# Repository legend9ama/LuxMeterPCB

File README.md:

# LuxMeter v1.0 - Hardware Datasheet

<div align="center">
  
</div>

**LuxMeter** started as a PCB design assignment for my *Fundamentals of Electronics* course.

The requirement was just to submit the layout files, but I decided to go all the way. I ordered the PCBAs and wrote the firmware.

This repository contains the hardware design files (KiCad), schematics, and manufacturing data.

---

## 📸 Gallery

| Top View | Bottom View |
| :---: | :---: |
|  | 

---

## 📐 Circuit Diagram (Schematic)

The full schematic design is available in the [`LuxMeter/`](./LuxMeter) folder.
<div align="center">
  
</div>

---

## 🛠 Hardware Specifications

### Component Overview
Datasheets for key components are stored locally in the [`docs/`](./docs) directory.

| Component | Part Number | Function | Interface | Datasheet |
| :--- | :--- | :--- | :--- | :--- |
| **MCU** | **STM32F030F4P6** | Main Controller (Cortex-M0) | - | [View PDF](./docs/stm32f030f4.pdf) |
| **Sensor** | **BH1750FVI** | Digital Light Sensor | I2C1 | [View PDF](./docs/bh1750fvi-e-186247.pdf) |
| **Display** | **SSD1306 / SH1106** | 0.96" OLED Module | I2C1 | [View PDF](./docs/ssd1306.pdf) |
| **SD Slot** | **Molex 104031-0811** | MicroSD Card Connector | SPI1 | [View PDF](./docs/1040310811_sd.pdf) |
| **Charger** | **MCP73831** | Li-Po Charge Controller | - | [View PDF](./docs/MCP73831-Family-Data-Sheet-DS20001984H.pdf) |
| **LDO** | **MCP1700-3.3V** | Voltage Regulator | - | [View PDF](./docs/MCP1700-Data-Sheet-20001826F.pdf) |
| **MOSFET** | **2N7002** | Battery Monitor Switch | GPIO | [View PDF](./docs/NDS7002A-D.PDF) |

---

## 🔌 GPIO Map (Bare Metal)

### GPIO Table

| Pin | Name | Schematic Label | Function | Active Level / Notes |
| :--- | :--- | :--- | :--- | :--- |
| **PF0** | `BTN_1` | `BTN_1` | User Button 1 | **Low** (Requires Internal Pull-Up) |
| **PF1** | `BTN_2` | `BTN_2` | User Button 2 | **Low** (Requires Internal Pull-Up) |
| **PA0** | `BATT_MON` | `BATT_MON` | ADC Input (Chan 0) | Analog Voltage (Divided by 2) |
| **PA1** | `LED_R` | `LED_R` | User LED (Red) | **High** |
| **PA2** | `BH_RST` | `BH_RST` | Sensor Reset / DVI | Check BH1750 Datasheet |
| **PA3** | `BATT_EN` | `BATT_EN` | Battery Monitor Enable | **High** (Enable measurement) |
| **PA4** | `SD_CS` | `SD_CS` | MicroSD Chip Select | **Low** (Software Controlled) |
| **PA5** | `SPI1_SCK` | `SPI1_SCK` | SPI Clock | AF0 |
| **PA6** | `SPI1_MISO` | `SPI1_MISO` | SPI MISO | AF0 |
| **PA7** | `SPI1_MOSI` | `SPI1_MOSI` | SPI MOSI | AF0 |
| **PB1** | `LED_G` | `LED_G` | User LED (Green) | **High** |
| **PA9** | `I2C1_SCL` | `I2C1_SCL` | I2C Clock | AF4 (Open-Drain) |
| **PA10** | `I2C1_SDA` | `I2C1_SDA` | I2C Data | AF4 (Open-Drain) |
| **PA13** | `SWDIO` | `SWDIO` | SWD Debug Data |  |
| **PA14** | `SWCLK` | `SWCLK` | SWD Debug Clock |   |

---

## ⚙️ Subsystem Details

### 1. Battery Monitoring
To extend battery life, the voltage divider (100kΩ/100kΩ) is disconnected via a MOSFET (`Q1`) when not in use.

* **Formula:** $V_{batt} = ADC_{val} \times \frac{3.3V}{4095} \times 2$
* **Sequence:**
    1.  Set `PA2` HIGH.
    2.  Wait ~1ms for stabilization.
    3.  Read ADC on `PA0`.
    4.  Set `PA2` LOW immediately.

### 2. MicroSD Interface (Molex 104031-0811)
The board uses a push-push type Molex connector.
* **Bus:** SPI1 (max 18 Mbps, start initialization at <400 kHz).
* **Card Detect:** Not physically connected. Use software polling (try to mount) to detect card insertion.

### 3. I2C Bus (Sensors)
* **BH1750 Address:** `0x23` (ADDR pin grounded).
* **OLED Address:** Typically `0x3C` (verify with I2C scanner).

---

## ⚠️ Errata & Assembly Notes (Rev 1.0)

**Important notes for assembling the v1.0 PCB:**

1.  **Capacitor C6 Interference:**
    * **Issue:** The decoupling capacitor `C6` is placed directly in the insertion path of the MicroSD card. The physical height of the component blocks the card from entering the Molex slot.
    * **Workaround:** Simply remove (desolder) `C6`. The SD card interface functions correctly without it.
    
2.  **Incorrect Connector Pitch (OLED & SWD):**
    * **Issue:** The through-hole footprints for the **OLED Display** and **SWD Debug** header connectors were incorrectly assigned a **1.0mm pitch** instead of the standard **2.54mm**.
    * **Workaround:** I soldered wires directly to the connectors.

---

## 📂 Repository Structure

* `LuxMeter/` — Original KiCad project files (Schematic & PCB).
* `gerbers/` — Production files (Gerber/Drill) for ordering PCBs.
* `docs/` — PDF datasheets for components.
* `images/` — Photos and diagrams used in this README.

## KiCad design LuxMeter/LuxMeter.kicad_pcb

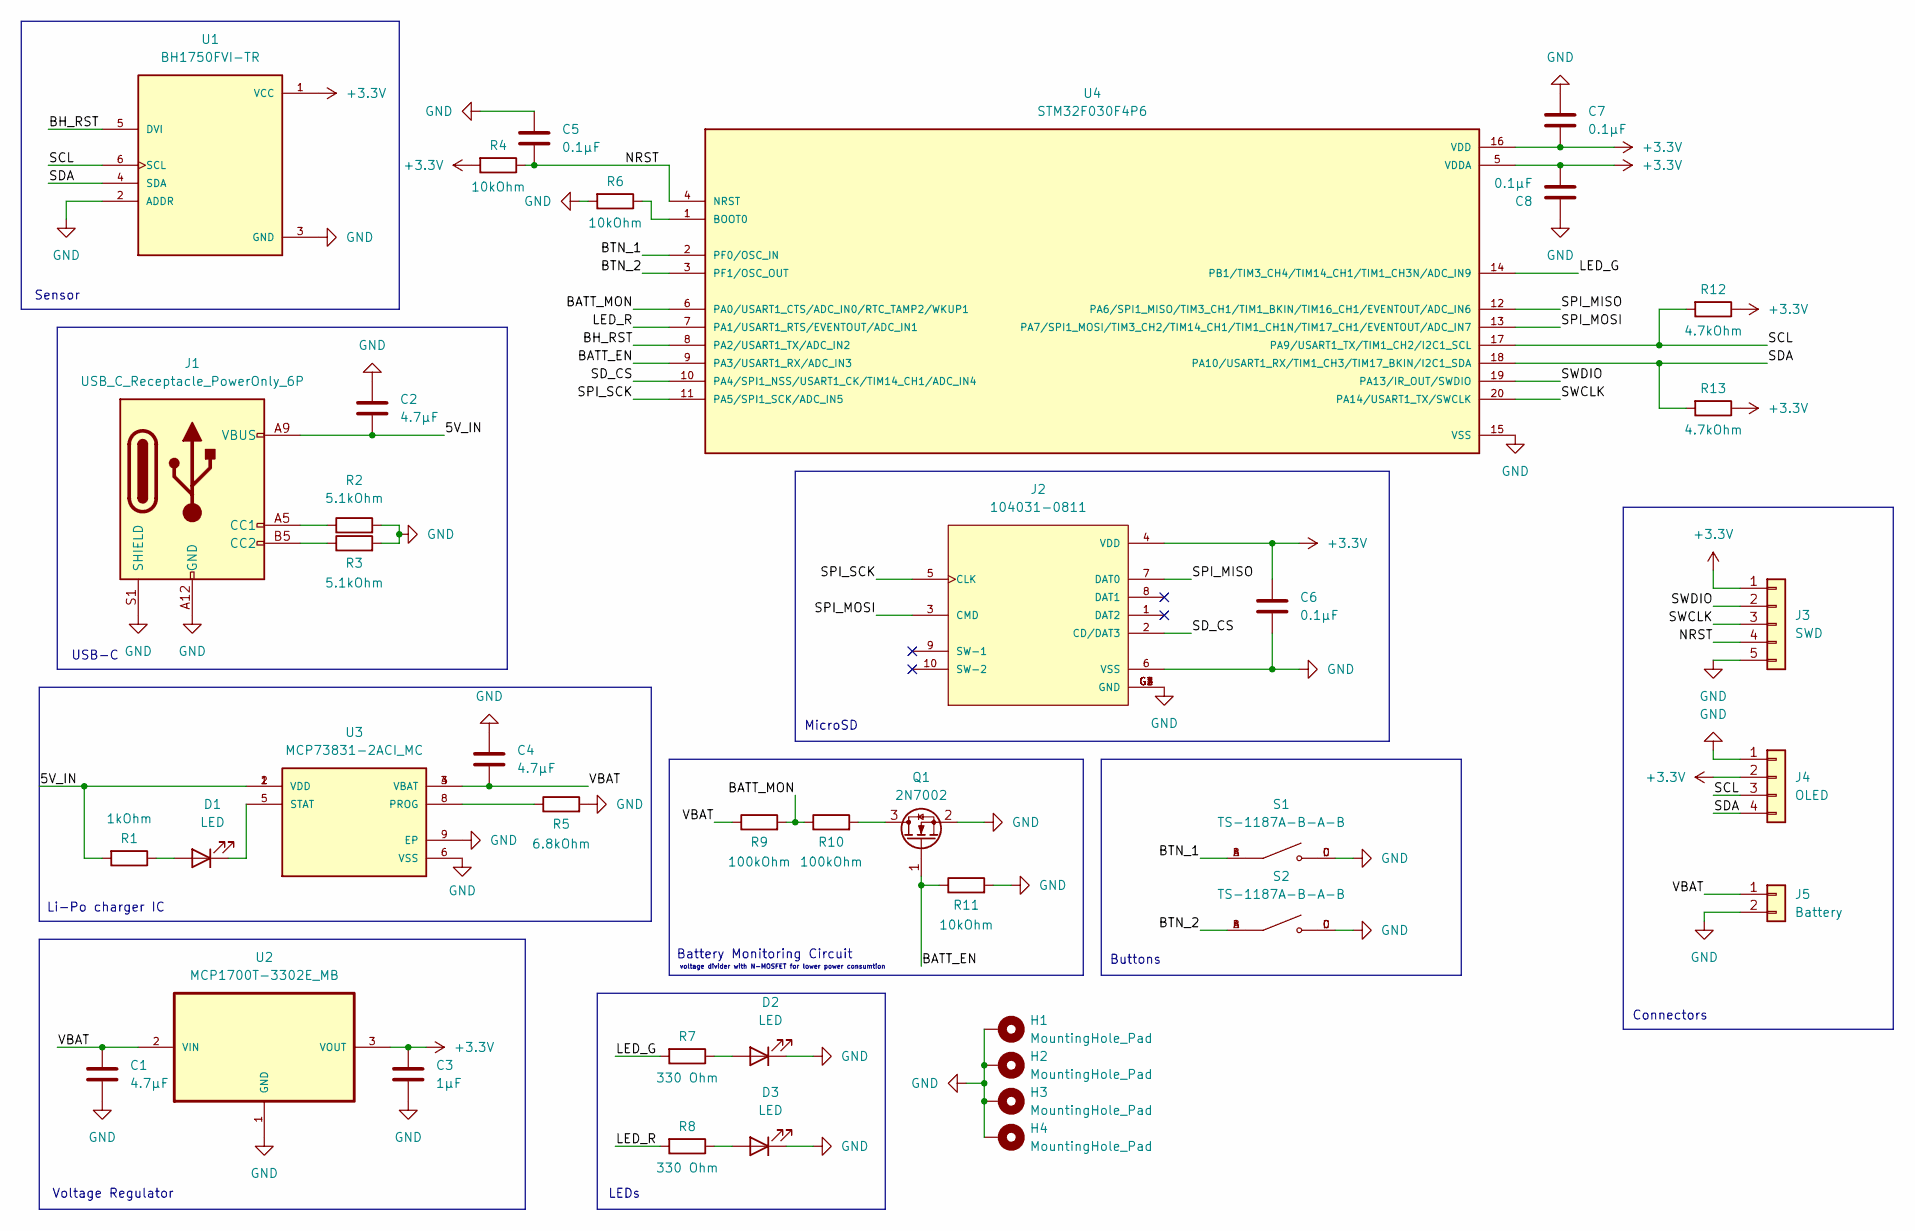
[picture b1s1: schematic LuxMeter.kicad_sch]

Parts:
C1, C2, C4: 4.7μF; C_0603_1608Metric
C3: 1μF; C_0603_1608Metric
C5, C6, C7, C8: 0.1μF; C_0603_1608Metric
D1, D2: LED; LED_0805_2012Metric
D3: LED; LED_0603_1608Metric
H1, H2, H3, H4: MountingHole_Pad; MountingHole_2.2mm_M2_Pad
J1: USB_C_Receptacle_PowerOnly_6P; CUI_UJC-HP-3-SMT-TR
J2: 104031-0811; MOLEX_104031-0811; PARTREV B2
J3: SWD; PinHeader_1x05_P1.00mm_Vertical
J4: OLED; PinHeader_1x04_P1.00mm_Vertical
J5: Battery; PinHeader_1x03_P1.00mm_Vertical
Q1: 2N7002; SOT-23
R1: 1kOhm; R_0603_1608Metric
R2, R3: 5.1kOhm; R_0603_1608Metric
R4, R6, R11: 10kOhm; R_0603_1608Metric
R5: 6.8kOhm; R_0603_1608Metric
R7, R8: 330 Ohm; R_0603_1608Metric
R9, R10: 100kOhm; R_0603_1608Metric
R12, R13: 4.7kOhm; R_0603_1608Metric
S1, S2: TS-1187A-B-A-B; SW_TS-1187A-B-A-B; PARTREV A0
U1: BH1750FVI-TR; XDCR_BH1750FVI-TR; PARTREV D
U2: MCP1700T-3302E_MB
U3: MCP73831-2ACI_MC; PARTREV G
U4: STM32F030F4P6; SOP65P640X120-20N

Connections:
+3.3V: C3.1, C6.1, C7.1, C8.1, J2.4 (VDD), J3.1, J4.2, R4.2, R12.1, R13.1, U1.1 (VCC), U2.3 (VOUT), U4.5 (VDDA), U4.16 (VDD)
/5V_IN: C2.1, J1.A9 (VBUS), J1.B9 (VBUS), R1.2, U3.1 (VDD), U3.2 (VDD)
/BATT_EN: Q1.1 (G), R11.1, U4.9 (PA3/USART1_RX/ADC_IN3)
/BATT_MON: R9.2, R10.1, U4.6 (PA0/USART1_CTS/ADC_IN0/RTC_TAMP2/WKUP1)
/BH_RST: U1.5 (DVI), U4.8 (PA2/USART1_TX/ADC_IN2)
/BTN_1: S1.A, S1.B, U4.2 (PF0/OSC_IN)
/BTN_2: S2.A, S2.B, U4.3 (PF1/OSC_OUT)
/LED_G: R7.2, U4.14 (PB1/TIM3_CH4/TIM14_CH1/TIM1_CH3N/ADC_IN9)
/LED_R: R8.2, U4.7 (PA1/USART1_RTS/EVENTOUT/ADC_IN1)
/NRST: C5.1, J3.4, R4.1, U4.4 (NRST)
/SCL: J4.3, R12.2, U1.6 (SCL), U4.17 (PA9/USART1_TX/TIM1_CH2/I2C1_SCL)
/SDA: J4.4, R13.2, U1.4 (SDA), U4.18 (PA10/USART1_RX/TIM1_CH3/TIM17_BKIN/I2C1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)
/SD_CS: J2.2 (CD/DAT3), U4.10 (PA4/SPI1_NSS/USART1_CK/TIM14_CH1/ADC_IN4)
/SPI_MISO: J2.7 (DAT0), U4.12 (PA6/SPI1_MISO/TIM3_CH1/TIM1_BKIN/TIM16_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)
/SPI_MOSI: J2.3 (CMD), U4.13 (PA7/SPI1_MOSI/TIM3_CH2/TIM14_CH1/TIM1_C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)
/SPI_SCK: J2.5 (CLK), U4.11 (PA5/SPI1_SCK/ADC_IN5)
/SWCLK: J3.3, U4.20 (PA14/USART1_TX/SWCLK)
/SWDIO: J3.2, U4.19 (PA13/IR_OUT/SWDIO)
/VBAT: C1.1, C4.2, J5.1, R9.1, U2.2 (VIN), U3.3 (VBAT), U3.4 (VBAT)
GND: C1.2, C2.2, C3.2, C4.1, C5.2, C6.2, C7.2, C8.2, D2.1 (K), D3.1 (K), H1.1, H2.1, H3.1, H4.1, J1.A12 (GND), J1.B12 (GND), J1.S1 (SHIELD), J2.6 (VSS), J2.G1 (GND), J2.G2 (GND), J2.G3 (GND), J2.G4 (GND), J3.5, J4.1, J5.2, Q1.2 (S), R2.2, R3.2, R5.2, R6.2, R11.2, S1.C, S1.D, S2.C, S2.D, U1.2 (ADDR), U1.3 (GND), U2.1 (GND), U3.6 (VSS), U3.9 (EP), U4.15 (VSS)
unnamed: D1.2 (A), R1.1
unnamed: D1.1 (K), U3.5 (STAT)
unnamed: D2.2 (A), R7.1
unnamed: D3.2 (A), R8.1
unnamed: J1.A5 (CC1), R2.1
unnamed: J1.B5 (CC2), R3.1
unnamed: Q1.3 (D), R10.2
unnamed: R5.1, U3.8 (PROG)
unnamed: R6.1, U4.1 (BOOT0)

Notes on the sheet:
voltage divider with N-MOSFET for lower power consumtion
Battery Monitoring Circuit
Connectors
USB-C
Voltage Regulator
Li-Po charger IC
Buttons
MicroSD
Sensor
LEDs

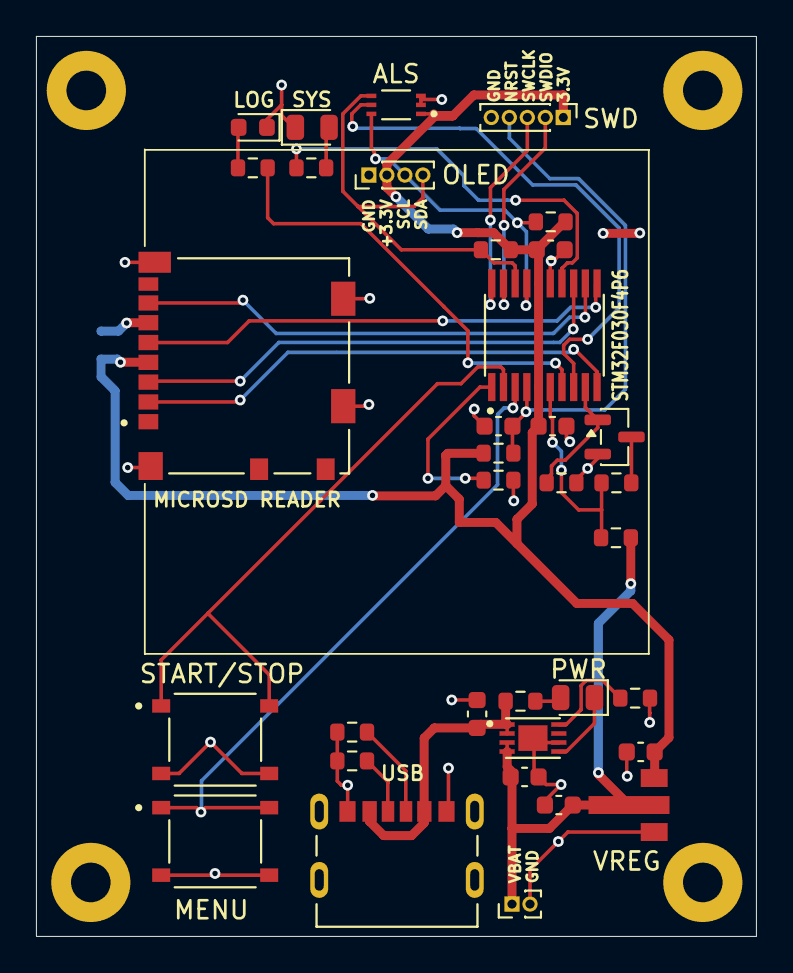
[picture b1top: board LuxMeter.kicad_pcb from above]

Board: 2 copper layers, 40.0 x 50.0 mm, 40 parts (1 on the bottom side), 29 nets.

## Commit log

2026-01-16 Init commit
